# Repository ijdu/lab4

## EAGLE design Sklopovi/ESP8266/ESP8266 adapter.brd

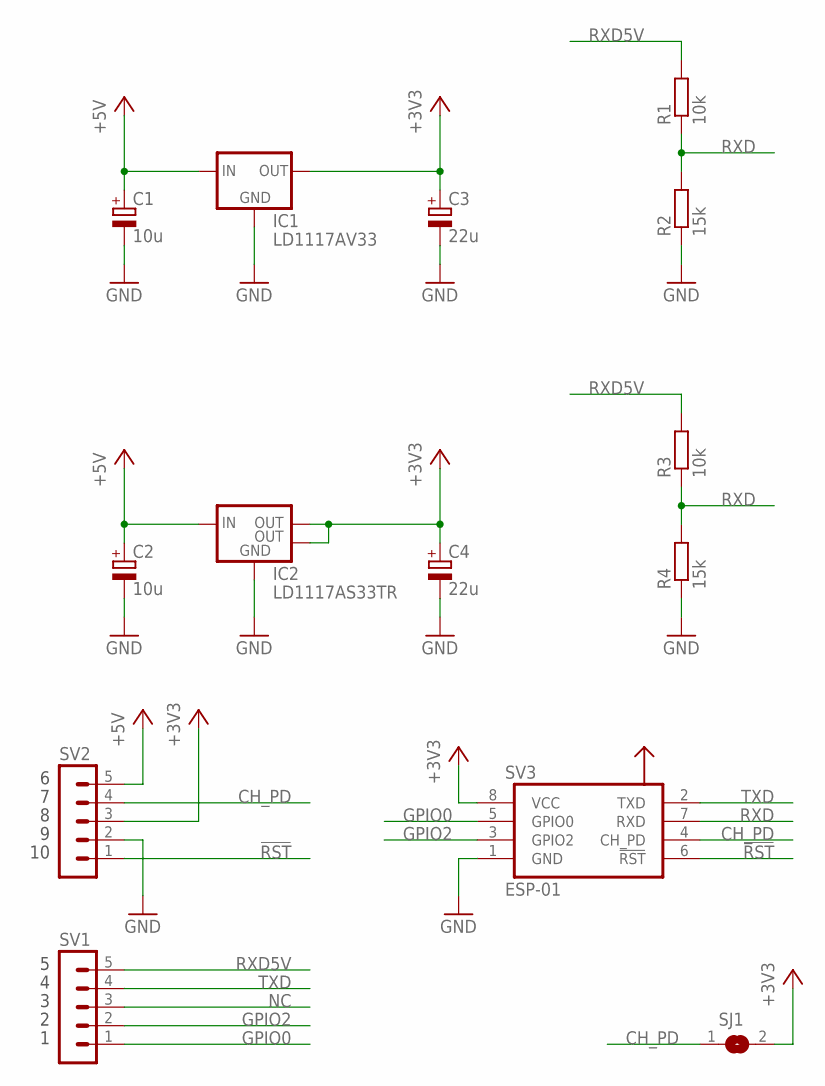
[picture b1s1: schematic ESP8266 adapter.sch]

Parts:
C1: 10u; E2,5-5
C2: 10u; A/3216-18W
C3: 22u; E2,5-5
C4: 22u; B/3528-21R
IC1: LD1117AV33; 78XXL
IC2: LD1117AS33TR; SOT223
R1: 10k; 0207/10
R2: 15k; 0207/10
R3: 10k; R1206
R4: 15k; R1206
SJ1: SJ
SV1, SV2: MA05-1
SV3: ESP-01; FE04-2

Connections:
!RST: SV2.1, SV3.6 (!RST)
+3V3: C3.+, C4.+, IC1.GND (OUT), IC2.2 (OUT), IC2.4 (OUT), SJ1.2, SV2.3, SV3.8 (VCC)
+5V: C1.+, C2.+, IC1.OUT (IN), IC2.3 (IN), SV2.5
CH_PD: SJ1.1, SV2.4, SV3.4 (CH_PD)
GND: C1.-, C2.-, C3.-, C4.-, IC1.IN (GND), IC2.1 (GND), R2.1, R4.1, SV2.2, SV3.1 (GND)
GPIO0: SV1.1, SV3.5 (GPIO0)
GPIO2: SV1.2, SV3.3 (GPIO2)
NC: SV1.3
RXD: R1.1, R2.2, R3.1, R4.2, SV3.7 (RXD)
RXD5V: R1.2, R3.2, SV1.5
TXD: SV1.4, SV3.2 (TXD)

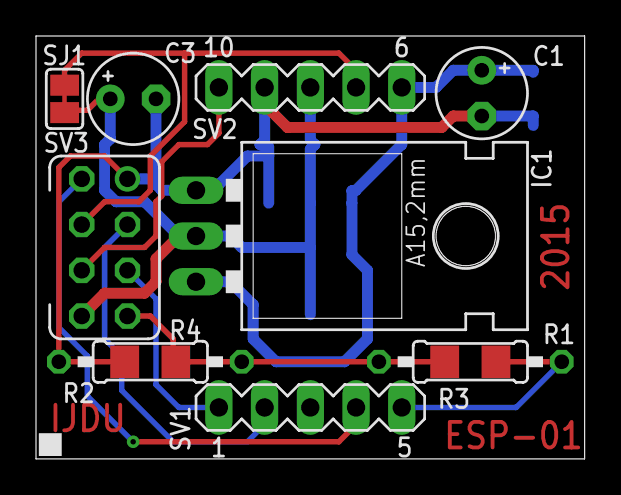
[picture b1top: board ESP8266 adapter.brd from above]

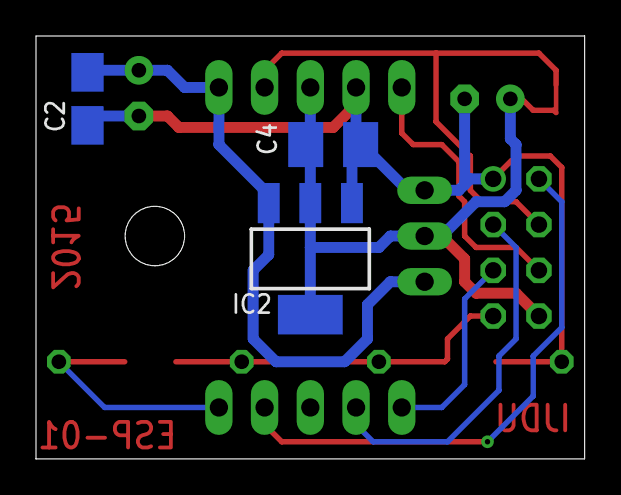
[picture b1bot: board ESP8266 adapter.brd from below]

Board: 2 copper layers, 30.5 x 23.5 mm, 14 parts (3 on the bottom side), 10 nets.

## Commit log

2016-04-27 prevent orphan lines
2016-04-27 add caption
2016-04-27 fix images leaving title alone
2016-04-28 fix photo on wrong page

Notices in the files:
parts and their libraries:
SparkFun-PowerIC: Licensing: Creative Commons ShareAlike 4.0 International - https://creativecommons.org/licenses/by-sa/4.0
